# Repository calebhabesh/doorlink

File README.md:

#  Doorlink

Living in an apartment without a concierge, you're often left guessing who's at the door, and asking questions like "did my package arrive?". Providing an interface for visitors to notify me of package deliveries and general presence is really convenient.

Doorlink is a self-hosted smart doorbell built around a custom ESP32-S3 board and a Raspberry Pi, with no cloud subscription required. A button press wakes the board, captures a still image, and sends the event to a local gateway. The gateway stores the media, updates the web dashboard, and sends ntfy notifications to household members. The doorbell plays a local chime; when configured, the gateway also sends a Home Assistant webhook to play a chime on all configured smart speakers in the home. Visitor recordings and stored, turn-based voice replies are also supported. A full parts and cost breakdown is in the [docs](docs/parts.md).

<p align="center">
  
  <br>
  <em>See the <a href="#hardware-gallery">labeled front panel</a>.</em>
</p>

## Demo

https://github.com/user-attachments/assets/69bbac34-c78c-457d-b82e-8ea92b961eb2

Recorded at my door on 2026-10-24: phone video of the doorbell beside a screen recording of the dashboard, synced and uncut. Part 1 shows a button press, the photo arriving, the desktop alert, and the Home Assistant chime. Part 2 shows a visitor voice message and a Push to Talk reply played back at the door. Each part ends with step timings from the gateway logs.

## Prototype Status

The assembled Rev C board is mounted at my door on battery power and in daily use. Each button press wakes the board from deep sleep, captures a QXGA image, uploads it over Wi-Fi, updates the dashboard, sends notifications, and returns to deep sleep. In the 30 days to 2026-10-24, the gateway stored a photo for all 27 presses, with a median of 2.9 s from the press alert reaching the gateway to the photo being stored. The single-cell battery has not been charged since installation: over the first four weeks and 97 presses it fell from roughly 78% to 46%, which projects to an average draw under 1 mA and about 12 weeks per charge. That is an estimate from an approximate starting reading and voltage-based percentages, not a measured current or an observed full-charge runtime. The microphone, speaker, and stored voice-reply path have been exercised on hardware. This is a working prototype, not a qualified outdoor product.

This is my first PCB layout and my first time hand-soldering surface-mount parts, including the ESP32-S3 module and ICS-43434 microphone. It took three revisions to get here: some scope creep, plus a few dumb mistakes that waited until after I ordered the boards to announce themselves.

## How It Fits Together

```mermaid
flowchart LR
    A[Doorbell PCB<br/>ESP32-S3 · camera · audio] -->|Wi-Fi| B[Raspberry Pi gateway<br/>Spring Boot]
    B --> C[(PostgreSQL<br/>events)]
    B --> D[(MinIO<br/>images and audio)]
    B --> E[Next.js dashboard]
    B --> F[ntfy notifications]
    A --> G[Local doorbell chime]
    B -->|Configured webhook| H[Home Assistant]
    H --> I[Smart speaker chimes]
    E -->|Stored voice replies| B
```

The firmware captures the image before joining Wi-Fi, then powers the camera down. Audio is turn-based: the visitor microphone and doorbell speaker do not run as a full-duplex call. The Raspberry Pi also runs Mosquitto for device commands.

### Household alerts

- The gateway sends an HTTP webhook to a Home Assistant automation, which plays a chime on all configured smart speakers in the home. This supplements the doorbell's local chime.
- Household members receive notifications through ntfy on their phones or computers, subscribed to a shared topic on ntfy.sh. Tapping a notification opens the Doorlink dashboard in their browser.

The home installation uses both alert paths. See [gateway environment configuration](docs/pi-deployment.md#gateway-environment) for the Home Assistant webhook and ntfy topic settings. The local development profile disables both integrations.

## Hardware Gallery

| Rev A | Rev B | Rev C |
| :---: | :---: | :---: |
|  |  |  |

All three revisions were assembled by JLCPCB and tested before settling on Rev C. Rev A to Rev B was the largest change, adding substantially more components. Rev B to Rev C corrected the mirrored pin mapping on the 24-pin camera FPC connector and made smaller optimizations. Images are KiCad 3D renders of each revision.

| Rev C Schematic |
| :---: |
|  |

| Copper Layers (F.Cu and B.Cu) | Rev C Before ESP32 and Mic Soldering | Front Lid Marked Out | Finished Front Panel |
| :---: | :---: | :---: | :---: |
|  |  |  |  |

| Bench Bring-Up | Populated PCB | Enclosure Wiring |
| :---: | :---: | :---: |
|  |  |  |

The board uses an ESP32-S3-WROOM-1-N16R8, OV5640 camera, ICS-43434 microphone, MAX98357A amplifier, MCP73871 charger, and TPS63802 3.3 V regulator. The [PCB overview](pcb/README.md) links the KiCad source and exact Rev C manufacturing files.

## Explore the Project

| Area | Contents |
| --- | --- |
| [`main/`](main/) | ESP-IDF firmware and routed board pin map |
| [`config/firmware/`](config/firmware/) | Firmware build presets and archived camera configurations |
| [`gateway/`](gateway/) | Spring Boot event API, persistence, media storage, and notifications |
| [`dashboard/`](dashboard/) | Next.js event and intercom interface |
| [`pcb/`](pcb/) | KiCad project and manufacturing records |
| [`docs/parts.md`](docs/parts.md) | Main unit parts and CAD cost |
| [`docs/firmware-architecture.md`](docs/firmware-architecture.md) | Firmware flow and validation status |
| [`docs/hardware-bringup.md`](docs/hardware-bringup.md) | Detailed Rev C hardware test record |

### Dashboard Preview (Synthetic Data)

<p align="center">
  
</p>

This preview uses synthetic session data and a generated doorbell-camera view. My actual dashboard is hosted on a subdomain with authenticated access. The [demo](#demo) shows it in presentation mode, which hides sessions from before the recording.

## Run Locally

Install Docker Compose, Java 21, Node.js with npm, and the dashboard dependencies (`cd dashboard && npm ci`). From the repository root, run `./scripts/run-dev.sh` to start the isolated development stack. The gateway uses port 8081 and the dashboard uses [localhost:3001](http://localhost:3001). On first run, enter the setup token printed by the launcher. Ctrl+C stops the stack. The local credentials in `.env.dev` are for development only.

Firmware builds require ESP-IDF. Copy `main/config.example.h` to the ignored `main/config.h`, set your Wi-Fi and gateway values, then see [firmware architecture](docs/firmware-architecture.md) for the safe and production build commands. Raspberry Pi deployment is documented in [docs/pi-deployment.md](docs/pi-deployment.md).

## License

Software and written documentation: [MIT](LICENSE). KiCad hardware designs and manufacturing files under `pcb/`: [CERN-OHL-P-2.0](pcb/LICENSE). [Project photographs](docs/media/README.md): [CC0 1.0](https://creativecommons.org/publicdomain/zero/1.0/).

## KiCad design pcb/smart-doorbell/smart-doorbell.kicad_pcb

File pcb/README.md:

# Doorlink PCB

The routed [KiCad schematic](smart-doorbell/smart-doorbell.kicad_sch) and [PCB](smart-doorbell/smart-doorbell.kicad_pcb) are the source for Rev C connections, footprints, and population intent. The Rev C design uses an ESP32-S3-WROOM-1-N16R8, an OV5640 24-pin camera connector, MCP73871 battery charging and power path, TPS63802 3.3 V regulation, and a GPIO-controlled camera power switch.

## Manufacturing files

The [Rev C ordered release](smart-doorbell/jlcpcb/rev-c/ORDERED_RELEASE.md) identifies the exact Gerber, JLCPCB BOM, and placement files submitted for the assembled prototype. Its BOM contains the 85 JLCPCB-populated references. U1 (ESP32-S3) and MK1 (microphone) were added after PCB assembly; several optional footprints remain unpopulated. The [protected assignment record](smart-doorbell/production/Smart_Doorbell_Project_B_bom-JLCPCB_FINAL.csv) retains per-reference LCSC assignments inherited from Rev B.

The [Rev B ordered release](smart-doorbell/jlcpcb/ORDERED_RELEASE.md) is historical. Its camera connector wiring differs from Rev C, so use the Rev C package for the photographed board. Do not regenerate or overwrite either ordered package.

The Rev C charger expects a suitable external 10 kΩ battery thermistor at J5; no thermistor is included in the PCB assembly BOM. See the [bring-up record](../docs/hardware-bringup.md) for the prototype checks and [board pin map](../main/board_pins.h) for firmware assignments.

Hardware design and manufacturing files in this directory: © 2026 Caleb Habesh, licensed under [CERN-OHL-P-2.0](LICENSE).

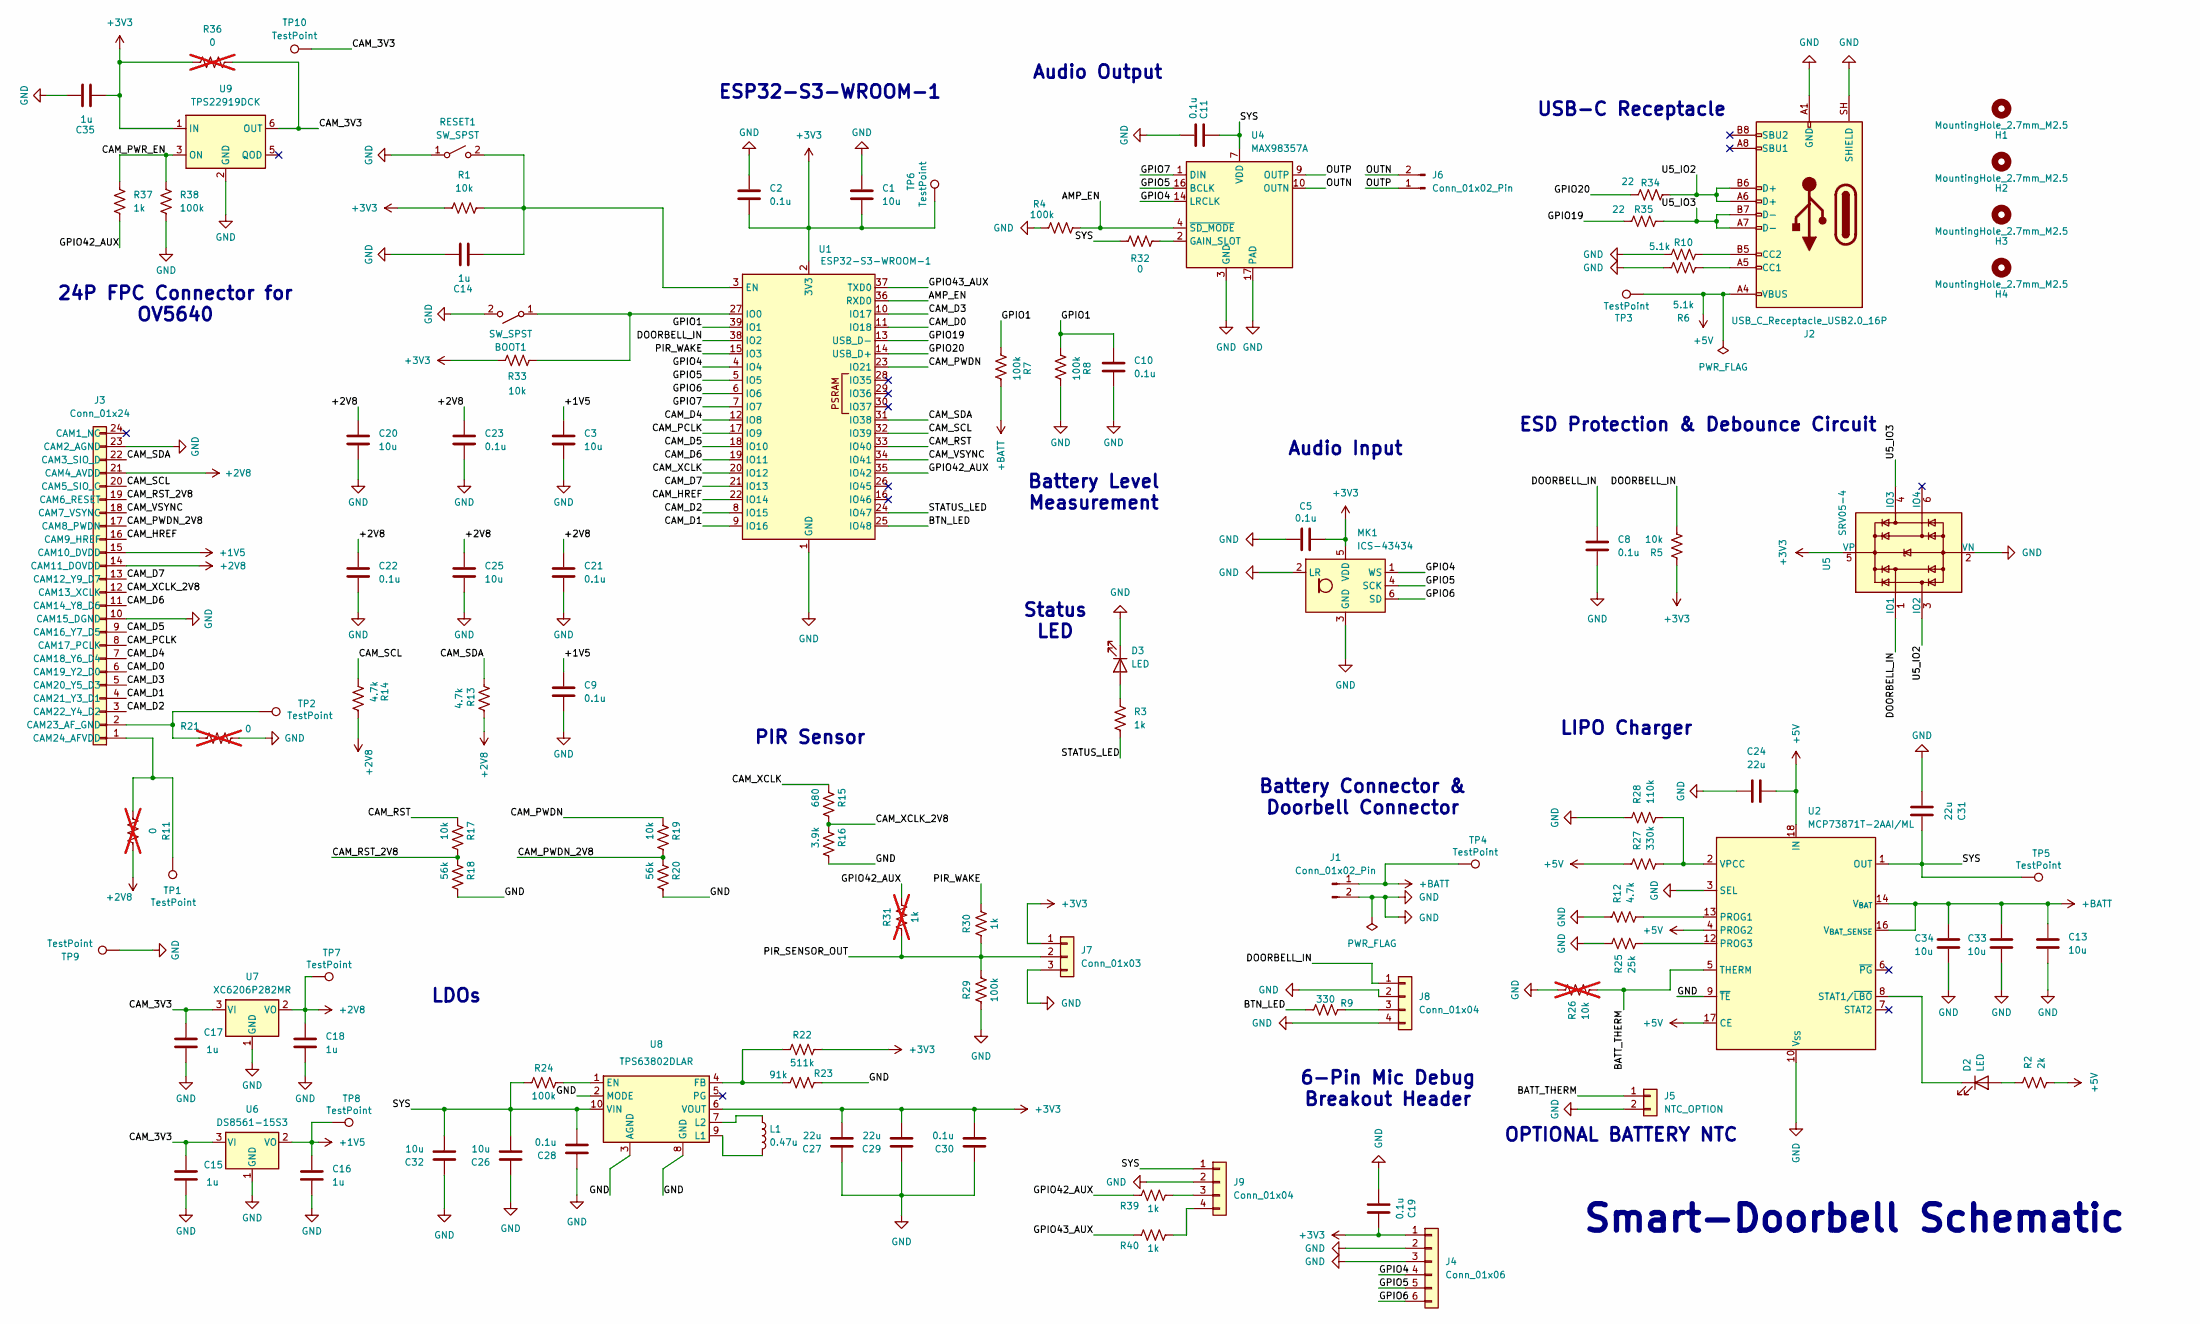
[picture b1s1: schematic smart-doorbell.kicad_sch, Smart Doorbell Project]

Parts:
BOOT1: SW_SPST; SW_SPST_B3U-1000P; LCSC Part # C231329
C1, C3, C13, C20, C25, C26, C33, C34: 10u; C_0603_1608Metric; LCSC Part # C19702
C2, C5, C8, C9, C10, C11, C19, C21, C22, C23, C28, C30: 0.1u; C_0603_1608Metric
C14, C15, C16, C17, C18, C35: 1u; C_0603_1608Metric
C24, C27, C29, C31: 22u; C_0603_1608Metric; LCSC Part # C84419
C32: 10u; C_0603_1608Metric; LCSC Part # C90053
D2, D3: LED; LED_0603_1608Metric
H1, H2, H3, H4: MountingHole_2.7mm_M2.5
J1, J6: Conn_01x02_Pin; JST_PH_B2B-PH-K_1x02_P2.00mm_Vertical; LCSC Part # C131337
J2: USB_C_Receptacle_USB2.0_16P; USB_C_Receptacle_HRO_TYPE-C-31-M-12; LCSC Part # C165948
J3: Conn_01x24; Hirose_FH12-24S-0.5SH_1x24-1MP_P0.50mm_Horizontal; LCSC Part # C202112
J4: Conn_01x06; PinHeader_1x06_P2.54mm_Vertical; LCSC Part # C37208
J5: NTC_OPTION; SolderWire-0.25sqmm_1x02_P4.2mm_D0.65mm_OD1.7mm
J7: Conn_01x03; JST_PH_B3B-PH-K_1x03_P2.00mm_Vertical; LCSC Part # C131339
J8: Conn_01x04; JST_PH_B4B-PH-K_1x04_P2.00mm_Vertical; LCSC Part # C131334
J9: Conn_01x04; PinHeader_1x04_P2.54mm_Vertical
L1: 0.47u; L_1008_2520Metric; MPN MHCH252010A-R47M-Q8; LCSC Part # C2981231
MK1: ICS-43434; InvenSense_ICS-43434-6_3.5x2.65mm
R1, R5, R17, R19, R33: 10k; R_0603_1608Metric; LCSC Part # C15401
R2: 2k; R_0603_1608Metric
R3, R30, R37, R39, R40: 1k; R_0603_1608Metric; LCSC Part # C21190
R4, R7, R8, R24, R29, R38: 100k; R_0603_1608Metric; LCSC Part # C25803
R6, R10: 5.1k; R_0603_1608Metric
R9: 330; R_0603_1608Metric
R11, R21: 0; R_0603_1608Metric; not fitted
R12, R13, R14: 4.7k; R_0603_1608Metric
R15: 680; R_0603_1608Metric
R16: 3.9k; R_0603_1608Metric
R18, R20: 56k; R_0603_1608Metric
R22: 511k; R_0603_1608Metric
R23: 91k; R_0603_1608Metric; LCSC Part # C23265
R25: 25k; R_0603_1608Metric
R26: 10k; R_0603_1608Metric; LCSC Part # C15401; not fitted
R27: 330k; R_0603_1608Metric
R28: 110k; R_0603_1608Metric
R31: 1k; R_0603_1608Metric; not fitted
R32: 0; R_0603_1608Metric; LCSC Part # C21189
R34, R35: 22; R_0603_1608Metric; LCSC Part # C23345
R36: 0; R_0603_1608Metric; LCSC Part # C21189; not fitted
RESET1: SW_SPST; SW_SPST_B3U-1000P; LCSC Part # C231329
TP1, TP2, TP3, TP4, TP5, TP6, TP7, TP8, TP9, TP10: TestPoint; TestPoint_Pad_D1.0mm
U1: ESP32-S3-WROOM-1
U2: MCP73871T-2AAI/ML; QFN-20-1EP_4x4mm_P0.5mm_EP2.5x2.5mm; MPN MCP73871T-2AAI/ML; LCSC Part # C144351
U4: MAX98357A; MAX98357A_TQFN-16-1EP_3x3mm_P0.5mm_EP1.23x1.23mm
U5: SRV05-4; SOT-23-6
U6: DS8561-15S3; SOT-23-3; MPN DS8561-15S3; LCSC Part # C5795628
U7: XC6206P282MR; SOT-23-3
U8: TPS63802DLAR; TPS63802DLAR_DLA0010A; MPN TPS63802DLAR; LCSC Part # C2845237
U9: TPS22919DCK; SOT-363_SC-70-6; LCSC Part # C2149796

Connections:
+1V5: C3.2, C9.2, C16.1, J3.15 (CAM10_DVDD), TP8.1 (1_1), U6.2 (VO)
+2V8: C18.1, C20.2, C21.2, C22.2, C23.2, C25.2, J3.14 (CAM11_DOVDD), J3.21 (CAM4_AVDD), R11.2, R13.2, R14.2, TP7.1 (1_1), U7.2 (VO)
+3V3: C1.2, C2.2, C5.1, C19.1, C27.1, C29.1, C30.1, C35.2, J4.1, J7.1, MK1.5 (VDD), R1.1, R5.1, R22.2, R33.1, R36.1, TP6.1 (1_1), U1.2 (3V3), U5.5 (VP), U8.6 (VOUT), U9.1 (IN)
+5V: C24.1, J2.A4 (VBUS), J2.A9 (VBUS), J2.B4 (VBUS), J2.B9 (VBUS), R2.2, R27.1, TP3.1 (1_1), U2.4 (PROG2), U2.17 (CE), U2.18 (IN), U2.19 (IN)
+BATT: C13.2, C33.2, C34.2, J1.1, R7.2, TP4.1 (1_1), U2.14 (V_{BAT}), U2.15 (V_{BAT}), U2.16 (V_{BAT_SENSE})
/AMP_EN: R4.2, U1.36 (RXD0), U4.4 (~SD_MODE)
/BATT_THERM: J5.1, R26.2, U2.5 (THERM)
/BTN_LED: R9.1, U1.25 (IO48)
/CAM_3V3: C15.1, C17.1, R36.2, TP10.1 (1_1), U6.3 (VI), U7.3 (VI), U9.6 (OUT)
/CAM_D0: J3.6 (CAM19_Y2_D0), U1.11 (IO18)
/CAM_D1: J3.4 (CAM21_Y3_D1), U1.9 (IO16)
/CAM_D2: J3.3 (CAM22_Y4_D2), U1.8 (IO15)
/CAM_D3: J3.5 (CAM20_Y5_D3), U1.10 (IO17)
/CAM_D4: J3.7 (CAM18_Y6_D4), U1.12 (IO8)
/CAM_D5: J3.9 (CAM16_Y7_D5), U1.18 (IO10)
/CAM_D6: J3.11 (CAM14_Y8_D6), U1.19 (IO11)
/CAM_D7: J3.13 (CAM12_Y9_D7), U1.21 (IO13)
/CAM_HREF: J3.16 (CAM9_HREF), U1.22 (IO14)
/CAM_PCLK: J3.8 (CAM17_PCLK), U1.17 (IO9)
/CAM_PWDN: R19.1, U1.23 (IO21)
/CAM_PWDN_2V8: J3.17 (CAM8_PWDN), R19.2, R20.1
/CAM_PWR_EN: R37.2, R38.2, U9.3 (ON)
/CAM_RST: R17.1, U1.33 (IO40)
/CAM_RST_2V8: J3.19 (CAM6_RESET), R17.2, R18.1
/CAM_SCL: J3.20 (CAM5_SIO_C), R14.1, U1.32 (IO39)
/CAM_SDA: J3.22 (CAM3_SIO_D), R13.1, U1.31 (IO38)
/CAM_VSYNC: J3.18 (CAM7_VSYNC), U1.34 (IO41)
/CAM_XCLK: R15.1, U1.20 (IO12)
/CAM_XCLK_2V8: J3.12 (CAM13_XCLK), R15.2, R16.1
/DOORBELL_IN: C8.1, J8.1, R5.2, U1.38 (IO2), U5.1 (IO1)
/GPIO1: C10.2, R7.1, R8.1, U1.39 (IO1)
/GPIO4: J4.4, MK1.1 (WS), U1.4 (IO4), U4.14 (LRCLK)
/GPIO5: J4.5, MK1.4 (SCK), U1.5 (IO5), U4.16 (BCLK)
/GPIO6: J4.6, MK1.6 (SD), U1.6 (IO6)
/GPIO7: U1.7 (IO7), U4.1 (DIN)
/GPIO19: R35.2, U1.13 (USB_D-)
/GPIO20: R34.2, U1.14 (USB_D+)
/GPIO42_AUX: R31.2, R37.1, R39.1, U1.35 (IO42)
/GPIO43_AUX: R40.1, U1.37 (TXD0)
/OUTN: J6.2, U4.10 (OUTN)
/OUTP: J6.1, U4.9 (OUTP)
/PIR_SENSOR_OUT: J7.2, R29.2, R30.1, R31.1
/PIR_WAKE: R30.2, U1.15 (IO3)
/STATUS_LED: R3.2, U1.24 (IO47)
/SYS: C11.2, C26.1, C28.1, C31.1, C32.1, J9.1, R24.1, R32.2, TP5.1 (1_1), U2.1 (OUT), U2.20 (OUT), U4.7 (VDD), U4.8 (VDD), U8.10 (VIN)
/U5_IO2: J2.A6 (D+), J2.B6 (D+), R34.1, U5.3 (IO2)
/U5_IO3: J2.A7 (D-), J2.B7 (D-), R35.1, U5.4 (IO3)
GND: BOOT1.2 (B), C1.1, C2.1, C3.1, C5.2, C8.2, C9.1, C10.1, C11.1, C13.1, C14.1, C15.2, C16.2, C17.2, C18.2, C19.2, C20.1, C21.1, C22.1, C23.1, C24.2, C25.1, C26.2, C27.2, C28.2, C29.2, C30.2, C31.2, C32.2, C33.1, C34.1, C35.1, D3.1 (K), J1.2, J2.A1 (GND), J2.A12 (GND), J2.B1 (GND), J2.B12 (GND), J2.SH (SHIELD), J3.10 (CAM15_DGND), J3.23 (CAM2_AGND), J4.2, J4.3, J5.2, J7.3, J8.2, J8.4, J9.2, MK1.2 (LR), MK1.3 (GND), R4.1, R6.2, R8.2, R10.2, R12.1, R16.2, R18.2, R20.2, R21.2, R23.2, R25.1, R26.1, R28.1, R29.1, R38.1, RESET1.1 (A), TP9.1 (1_1), U1.1 (GND), U1.40 (GND), U1.41 (GND), U2.3 (SEL), U2.9 (~TE), U2.10 (V_{SS}), U2.11 (V_{SS}), U2.21 (V_{SS}), U4.3 (GND), U4.11 (GND), U4.15 (GND), U4.17 (PAD), U5.2 (VN), U6.1 (GND), U7.1 (GND), U8.2 (MODE), U8.3 (AGND), U8.8 (GND), U9.2 (GND)
unnamed: BOOT1.1 (A), R33.2, U1.27 (IO0)
unnamed: D2.2 (A), R2.1
unnamed: D2.1 (K), U2.8 (STAT1/~LBO)
unnamed: D3.2 (A), R3.1
unnamed: J2.A5 (CC1), R6.1
unnamed: J2.B5 (CC2), R10.1
unnamed: J3.2 (CAM23_AF_GND), R21.1, TP2.1 (1_1)
unnamed: J3.1 (CAM24_AFVDD), R11.1, TP1.1 (1_1)
unnamed: J8.3, R9.2
unnamed: J9.3, R39.2
unnamed: J9.4, R40.2
unnamed: C14.2, R1.2, RESET1.2 (B), U1.3 (EN)
unnamed: R12.2, U2.13 (PROG1)
unnamed: R25.2, U2.12 (PROG3)
unnamed: R27.2, R28.2, U2.2 (VPCC)
unnamed: R32.1, U4.2 (GAIN_SLOT)
unnamed: R24.2, U8.1 (EN)
unnamed: R22.1, R23.1, U8.4 (FB)
unnamed: L1.2, U8.9 (L1)
unnamed: L1.1, U8.7 (L2)

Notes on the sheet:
Battery Level Measurement
LDOs
Audio Input
USB-C Receptacle
Audio Output
ESD Protection & Debounce Circuit
6-Pin Mic Debug Breakout Header
Battery Connector & Doorbell Connector
24P FPC Connector for OV5640
PIR Sensor
OPTIONAL BATTERY NTC
Smart-Doorbell Schematic
LIPO Charger
Status LED
ESP32-S3-WROOM-1

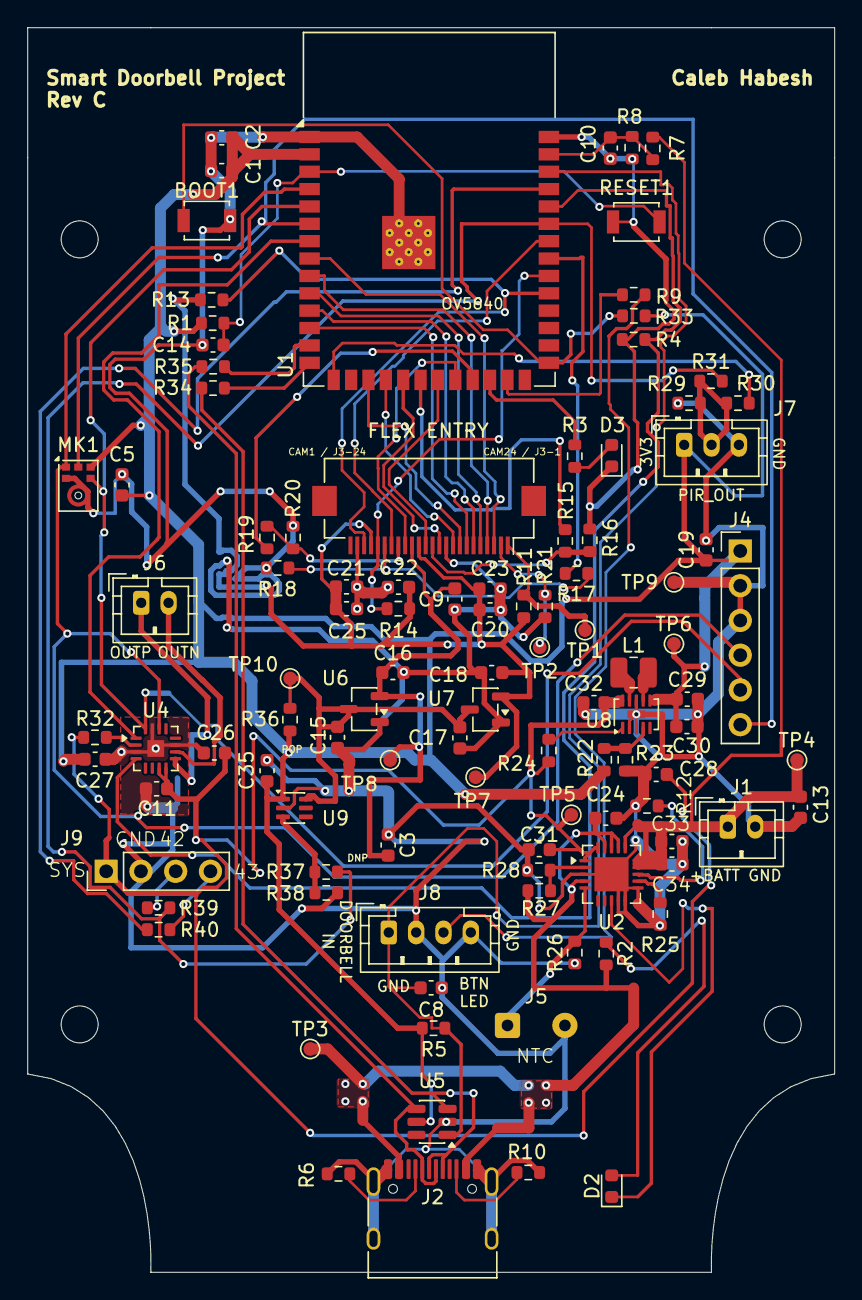
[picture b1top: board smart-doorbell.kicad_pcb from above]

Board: 2 copper layers, 59.0 x 91.0 mm, 108 parts (0 on the bottom side), 68 nets.

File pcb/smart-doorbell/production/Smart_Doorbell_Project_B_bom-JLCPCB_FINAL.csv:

Designator,Footprint,Quantity,Value,LCSC Part #
"BOOT1, RESET1",SW_SPST_B3U-1000P,2,SW_SPST,C231329
"C1, C13, C20, C25, C26, C3, C33, C34",0603,8,10u,C19702
"C10, C11, C19, C2, C21, C22, C23, C28, C30, C5, C8, C9",0603,12,0.1u,C14663
"C14, C15, C16, C17, C18",0603,5,1u,C15849
"C24, C27, C29, C31",0603,4,22u,C84419
C32,0603,1,10u,C90053
"D2, D3",0603,2,LED,C2290
"J1, J6",JST_PH_B2B-PH-K_1x02_P2.00mm_Vertical,2,Conn_01x02_Pin,C131337
J2,USB_C_Receptacle_HRO_TYPE-C-31-M-12,1,USB_C_Receptacle_USB2.0_16P,C165948
J3,Hirose_FH12-24S-0.5SH_1x24-1MP_P0.50mm_Horizontal,1,Conn_01x24,C202112
J4,PinHeader_1x06_P2.54mm_Vertical,1,Conn_01x06,C37208
J7,JST_PH_B3B-PH-K_1x03_P2.00mm_Vertical,1,Conn_01x03,C131339
J8,JST_PH_B4B-PH-K_1x04_P2.00mm_Vertical,1,Conn_01x04,C131334
L1,1008,1,0.47u,C2981231
"R1, R17, R19, R26, R33, R5",0603,6,10k,C15401
"R10, R6",0603,2,5.1k,C23186
"R12, R13, R14",0603,3,4.7k,C23162
R15,0603,1,680,C23228
R16,0603,1,3.9k,C23018
"R18, R20",0603,2,56k,C23206
R2,0603,1,2k,C22975
R22,0603,1,511k,C23194
R23,0603,1,91k,C23265
"R24, R29, R38, R4, R7, R8",0603,6,100k,C25803
R25,0603,1,25k,C2828637
R27,0603,1,330k,C23137
R28,0603,1,110k,C25805
"R3, R30, R39, R40",0603,4,1k,C21190
"R32, R36",0603,2,0,C21189
"R34, R35",0603,2,22,C23345
R9,0603,1,330,C23138
U2,QFN-20-1EP_4x4mm_P0.5mm_EP2.5x2.5mm,1,MCP73871T-2AAI/ML,C144351
U4,MAX98357A_TQFN-16-1EP_3x3mm_P0.5mm_EP1.23x1.23mm,1,MAX98357A,C910544
U5,SOT-23-6,1,SRV05-4,C7420376
U6,SOT-23-3,1,DS8561-15S3,C5795628
U7,SOT-23-3,1,XC6206P282MR,C347374
U8,TPS63802DLAR_DLA0010A,1,TPS63802DLAR,C2845237

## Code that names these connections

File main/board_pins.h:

#pragma once

#include "driver/gpio.h"

/*
 * Board pin map generated from pcb/smart-doorbell/smart-doorbell.net.
 * The ESP32-S3 GPIO matrix makes many peripherals remappable, but after PCB
 * fabrication these constants must match the routed nets.
 */

// Wake/button and indicators
#define DOORBELL_BUTTON_PIN GPIO_NUM_2   // /DOORBELL_IN
#define BATTERY_ADC_PIN     GPIO_NUM_1   // /GPIO1, 100k/100k divider
#define PIR_WAKE_PIN        GPIO_NUM_3   // /PIR_WAKE, J7.2 through populated R30
#define PIR_OUT_PIN         PIR_WAKE_PIN // Compatibility alias for existing firmware
#define STATUS_LED_PIN      GPIO_NUM_47  // /STATUS_LED
#define BUTTON_LED_PIN      GPIO_NUM_48  // /BTN_LED

// MAX98357A amplifier control
#define AMP_EN_PIN          GPIO_NUM_44  // /AMP_EN -> MAX98357A SD_MODE

// OV5640 camera on 24-pin FPC J3
#define CAM_PWR_EN_PIN      GPIO_NUM_42  // /GPIO42_AUX -> R37 -> /CAM_PWR_EN (Rev C)
#define CAM_PIN_D0          18           // /CAM_D0
#define CAM_PIN_D1          16           // /CAM_D1
#define CAM_PIN_D2          15           // /CAM_D2
#define CAM_PIN_D3          17           // /CAM_D3
#define CAM_PIN_D4          8            // /CAM_D4
#define CAM_PIN_D5          10           // /CAM_D5
#define CAM_PIN_D6          11           // /CAM_D6
#define CAM_PIN_D7          13           // /CAM_D7
#define CAM_PIN_PCLK        9            // /CAM_PCLK
#define CAM_PIN_XCLK        12           // /CAM_XCLK
#define CAM_PIN_HREF        14           // /CAM_HREF
#define CAM_PIN_PWDN        21           // /CAM_PWDN
#define CAM_PIN_SIOD        38           // /CAM_SDA
#define CAM_PIN_SIOC        39           // /CAM_SCL
#define CAM_PIN_RESET       40           // /CAM_RST
#define CAM_PIN_VSYNC       41           // /CAM_VSYNC

/*
 * Rev C populates R37 and leaves R31 DNP, dedicating GPIO42 to camera power.
 * Do not enable the GPIO42 PIR fallback while R37 is populated.
 */

// I2S audio
#define I2S_AUDIO_WS        GPIO_NUM_4   // /GPIO4 -> ICS WS, MAX LRCLK
#define I2S_AUDIO_SCK       GPIO_NUM_5   // /GPIO5 -> ICS SCK, MAX BCLK
#define I2S_MIC_SD          GPIO_NUM_6   // /GPIO6 -> ICS SD
#define I2S_SPK_SD          GPIO_NUM_7   // /GPIO7 -> MAX DIN

// Native USB. Reserved for USB only.
#define USB_D_MINUS_PIN     GPIO_NUM_19
#define USB_D_PLUS_PIN      GPIO_NUM_20

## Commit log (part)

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2026-04-29 initialized new project using the esp idf extension blank template
2026-04-29 chore: initialize spring boot gateway skeleton
2026-04-29 chore: initialize next.js dashboard skeleton
2026-04-29 chore: setup esp-idf firmware placeholders
2026-05-01 feat(firmware): implement I2S audio initialization
    - Added driver/i2s_std.h include
    - Defined I2S pins for INMP441 mic and MAX98357A speaker
    - Created init_i2s() to configure 16kHz 16-bit Mono channels
    - Integrated audio initialization into app_main
2026-05-01 feat(firmware): implement wifi and mqtt connectivity
    - Added config.example.h for network credentials
    - Updated .gitignore to exclude config.h
    - Implemented init_wifi() with event group blocking
    - Implemented init_mqtt() with basic event handler
    - Added NVS initialization required for WiFi
2026-05-01 feat: add s3 configuration for minio
2026-05-01 feat: create Event entity and repository
2026-05-01 feat: add EventController to handle image uploads
2026-05-01 fix: resolve failing context and tests
2026-05-02 feat: implement http multipart upload client
2026-05-02 feat: integrate dummy image upload into main flow
2026-05-02 chore: add mqtt configuration properties
2026-05-02 feat: configure spring integration mqtt beans
2026-05-02 feat: add inbound mqtt adapter configuration
2026-05-02 feat: add SSE stream, history endpoint, and CORS config
2026-05-02 feat: implement focus mode dashboard ui with sse
2026-05-02 fix: disable WRITE_DATES_AS_TIMESTAMPS for proper json date string via SSE
2026-05-02 feat: revamp dashboard ui with modern glassmorphism aesthetic
2026-05-02 feat: implement enterprise siem dashboard layout with custom svg
2026-05-02 feat: implement dashboard ui iterations based on user feedback
2026-05-02 style: fix grid visibility, add dark scrollbar, align recent log height
2026-05-02 style: scale up media card and fix recent log scroll behavior using absolute inset trick
2026-05-02 style: final scaling and scroll fixes for enterprise dashboard
2026-05-02 style: add smooth gradient mask to recent log list
2026-05-03 refactor: extract sidebar and main layout into reusable components
2026-05-03 feat: scale up event log table and update site brand icon
2026-05-03 feat: use custom ring-doorbell svg for site brand icon
2026-05-03 style: shrink main card and log box, fix two-tone icon gradient
2026-05-03 style: shrink dashboard 25%, fix absolute inset trick, and correct brand icon gradient
2026-05-03 chore: ignore .worktrees directory
2026-05-03 feat: update sidebar navigation links
2026-05-03 fix: timezone offset bug and wrap filteredEvents in useMemo
2026-05-03 feat: add calendar view page with mocked data
2026-05-03 feat: add system health dashboard page
2026-05-03 feat: add system settings page with mock configurations
2026-05-03 fix: resolve toast race condition in settings page
2026-05-03 fix: resolve merge conflicts and typescript errors
2026-05-04 feat: implement asynchronous NtfyService
2026-05-04 feat: add audio file handling and trigger ntfy notifications
2026-05-04 fix: resolve hardcoded dates in calendar view
2026-05-05 test: add virtual ESP32 script and wire frontend audio playback
2026-05-05 chore: configure ntfy topic in properties
2026-05-05 feat: polish ntfy notification message text
2026-05-05 docs: define and document the audio interaction model
2026-05-13 feat: integrate custom PCB design and architecture updates
    - Add KiCad project files, gerbers, and production files for the custom PCB
    - Update .gitignore to exclude KiCad backups, temp scripts, and superpower states
    - Update README.md and GEMINI.md to reflect the shift to the ESP32-S3-WROOM-1-N16R8, including its specific trace-optimized camera and audio pinout mappings
    - Add development plans and updated gateway wrapper/lock files
    - Minor firmware UI/settings tweaks to support updated component mappings
2026-05-14 build: bump java target to 21
2026-05-14 fix(ui): use dynamic hostname for api and minio urls
2026-05-14 style(ui): add slide-in animations to remaining dashboard pages
2026-05-14 style(ui): standardize animations across all pages using flash effect
2026-05-16 build: remove devtools to fix classloader crash on ARM/Java21
2026-05-16 build: force byte-buddy 1.14.13 to resolve ARM64 classloading bug
2026-05-16 feat(dashboard): implement internal API proxy for secure WAN access
    This change routes all /api requests through the Next.js server, allowing the dashboard to function behind Cloudflare Tunnels without exposing port 8080.
2026-05-16 docs: sync project state, correct pinouts, and document workflow
    This commit saves the documentation and configuration cleanups performed by the subagent, ensuring the README, bring-up checklist, and deployment docs accurately reflect the current Arch/Pi workflow 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
2026-05-16 docs(pcb): append final JLCPCB manufacturing BOM and AliExpress sourcing costs
2026-05-16 fix(deploy): update systemd user and paths to ethioprince for Pi deployment
2026-05-16 fix(backend): disable proxy buffering for SSE stream to fix dashboard event animation
    Adds X-Accel-Buffering: no and Cache-Control headers to the /stream endpoint so that Next.js and Cloudflare tunnels do not buffer the Server-Sent Events, allowing the dashboard to update in real-time.
2026-05-16 Fix live event updates and document systemd workflow
2026-05-16 style(dashboard): add smooth fade-in transition and loading state for event images
    This prevents the black flicker when loading larger JPEG payloads from the doorbell camera by displaying a loading spinner and applying a CSS blur/opacity transition once the Next.js Image component 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
2026-05-16 fix(dashboard): restore missing isImageLoaded state variable
    A previous commit failed to inject the state definition, causing a ReferenceError during render.
2026-05-16 feat(backend): implement automated storage retention to prevent SD card overflow
    Adds a scheduled task that runs daily at 3 AM to permanently delete events and their associated MinIO media files if they are older than 30 days.
2026-05-18 feat(dashboard): update metadata and replace default favicon
    Sets the proper application title/description and uses a custom SVG icon for the dashboard instead of the default Next.js assets.
2026-05-18 fix(dashboard): resolve missing imports and state in event log page
2026-05-18 feat(dashboard): implement responsive mobile layout
    Adds a mobile top bar with slide-out drawer navigation to MainLayout, makes the home page vertically scrollable on mobile, and adds a card-based mobile view for the Event Log to ensure usability with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
2026-05-18 fix(dashboard): restore missing onNavigate prop definition in Sidebar component
2026-05-18 style(dashboard): fix awkward entry animations on event lists
    Restricts the 'animate-slide-in' class so that it only applies to newly arriving live events, rather than animating every single historical row or card when the page first loads.
2026-05-18 feat(dashboard): enhance calendar view with date jumper and preview drawer
    Fixes the Event Log wrapper flicker by deferring the animate-flash-event class until loading completes. Adds an HTML month input to the Calendar header to quickly jump dates, and upgrades the Calenda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
2026-05-18 style(dashboard): fix layout clipping and mobile header spacing
    Adds overflow-hidden to MainLayout to prevent the grid background from bleeding out of the rounded corner. Adjusts the flex wrapping and padding on the mobile headers in Event Log and Calendar views 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
2026-05-18 style(dashboard): finalize mobile header branding and fix dropdown alignment
    Uses the correct speaker logo in the mobile header, expands the mobile status indicator with full text, fixes the toggle switch alignment in Settings, and corrects lopsided dropdown arrows by using c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
2026-05-18 style(dashboard): finalize UI branding and alignment fixes
    Cleans up Sidebar.tsx JSX structure, fixes toggle switch alignment in Settings, and implements custom dropdown arrows for better visual balance.
2026-05-19 style(dashboard): extend content grid to the right edge of the screen
2026-05-19 style(dashboard): align sidebar with content and make log header opaque
    Removes the vertical margin from the main layout to align perfectly with the sidebar and updates the recent log header to be opaque zinc-900 with a subtle border to prevent content phasing.
2026-05-19 style(dashboard): align main content to edges while keeping top-left curve
2026-05-19 style(dashboard): transparent log header with scroll masking
    Moves the Recent Log header outside the scrollable area and sets it to transparent to reveal the grid background. Implements a dual-sided linear-gradient mask on the scroll container so entries smoot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
2026-05-19 style(dashboard): improve mobile UI for date pickers and toggle switch
    Overhauls the date pickers in Event Log and Calendar views to be more prominent and clearly labeled with icons. Standardizes the toggle switch in Settings for a better mobile look and feel.
2026-05-19 style(dashboard): refine mobile spacing and fix squished date arrows
    Increases the gap between settings text and toggles, and adds right-padding/margin to native date pickers to ensure the dropdown arrows are properly aligned and not squished against the border.
2026-05-19 Enable Home Assistant chime provider
2026-05-19 style(dashboard): refine scrollbar and custom date picker arrows
    Darkens the recent log scrollbar track to match the site theme. Replaces the native browser date picker arrow with a custom Lucide ChevronDown icon to ensure perfect alignment across all mobile brows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
2026-05-20 feat(gateway): implement real system settings, health checks, and event retention
2026-05-20 feat(dashboard): implement functional health and settings pages with backend support
2026-05-20 feat: implement API key security and improve WiFi robustness
2026-05-20 security(remediations): resolve audit findings, restrict CORS, extend API key checks, template secrets, downsample PTT to 16kHz PCM, clean tests
2026-05-20 security(remediations): sanitize example secrets, enforce fail-closed configuration in systemd services
2026-05-20 fix(firmware): enable octal flash in defaults to align with N16R8 module
2026-05-23 fix(dashboard): prevent text selection on Push to Talk button during long press
2026-05-23 style(dashboard): shrink active event bottom bar on mobile, center text metadata, and enforce 12-hour clock format
2026-05-23 style(dashboard): enlarge mobile buttons to full size and format active event timestamp with a comma after the day of the week
2026-05-23 style(dashboard): enlarge Play Audio and Push to Talk buttons for easier tap targets on all devices
2026-05-23 style(dashboard): set spacious fixed heights and equal widths on mobile action buttons
2026-05-23 style(dashboard): restore original horizontal layout and size for desktop viewports on action buttons
2026-05-28 style(dashboard): rearrange active event page grid layout and add mobile responsive hide/show rules
2026-05-28 Configure isolated local dev environment on Arch
2026-05-29 feat(dashboard): add compact mobile battery indicators in header and status grid
2026-05-29 style(dashboard): move mobile battery/wifi widgets below media and fix system live text centering
2026-05-29 style(logo): remove boxed borders and add pulsing glow behind brand logo
2026-05-29 style(typography): import Sora google font and apply to Smart Doorbell branding header text
2026-05-29 brand: rename user-facing text and metadata to Doorlink
2026-05-29 style(typography): update brand text typeface to Space Grotesk and increase size
2026-05-29 fix(dashboard): stop overlapping audio playback on click and reset on event change
2026-05-29 docs: add half duplex intercom architecture spec sheet
2026-06-20 patch repo units for pi
2026-06-20 env issues
